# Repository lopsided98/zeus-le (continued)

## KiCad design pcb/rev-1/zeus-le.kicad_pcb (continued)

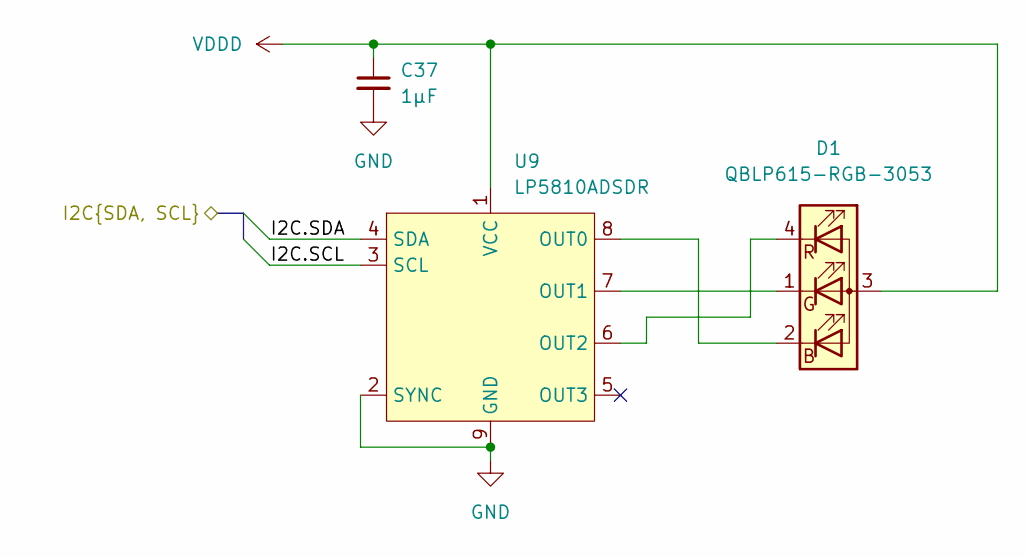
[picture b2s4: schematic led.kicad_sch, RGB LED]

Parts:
C37: 1µF; C_0603_1608Metric
D1: QBLP615-RGB-3053; LED_QBLP615-RGB-3053
U9: LP5810ADSDR; WSON-8-1EP_3x3mm_P0.65mm_EP1.65x2.4mm_ThermalVias

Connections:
/Audio/I2C.SCL: U9.3 (SCL); also elsewhere on the board
/Audio/I2C.SDA: U9.4 (SDA); also elsewhere on the board
GND: C37.2, U9.2 (SYNC), U9.9 (GND); also elsewhere on the board
unnamed: D1.2 (BK), U9.8 (OUT0)
unnamed: D1.1 (GK), U9.7 (OUT1)
unnamed: D1.4 (RK), U9.6 (OUT2)
VDDD: C37.1, D1.3 (A), U9.1 (VCC); also elsewhere on the board

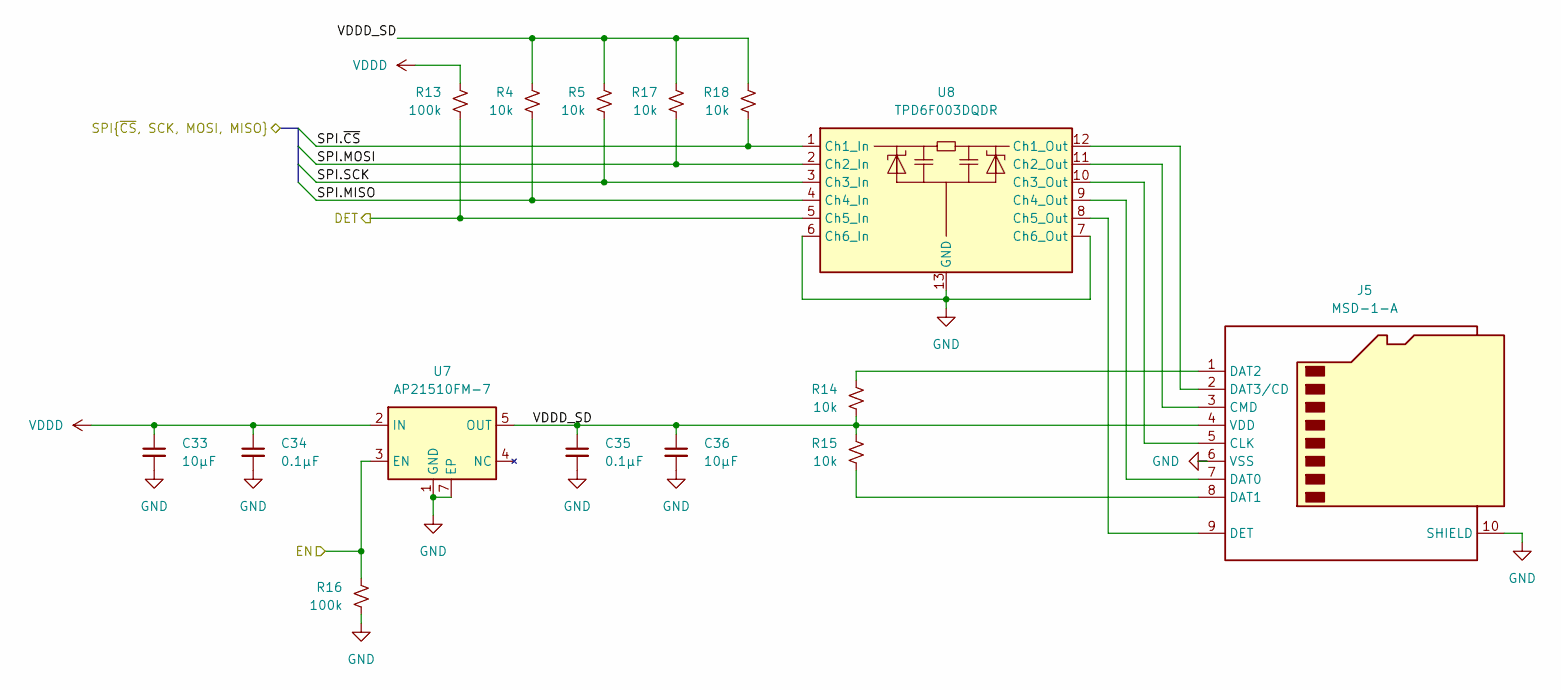
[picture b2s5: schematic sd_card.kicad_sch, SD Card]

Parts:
C33, C36: 10µF; C_0603_1608Metric
C34, C35: 0.1µF; C_0402_1005Metric
J5: MSD-1-A; microSD_HC_CUI_MSD-1-A
R4, R5, R14, R15, R17, R18: 10k; R_0402_1005Metric
R13, R16: 100k; R_0402_1005Metric
U7: AP21510FM-7; Diodes_UDFN2018-6
U8: TPD6F003DQDR; Texas_R-PWSON-N12_EP0.4x2mm; digikey# 296-25802-1-ND

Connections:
/MCU/SD.MISO: R4.2, U8.4 (Ch4_In); also elsewhere on the board
/MCU/SD.MOSI: R17.2, U8.2 (Ch2_In); also elsewhere on the board
/MCU/SD.SCK: R5.2, U8.3 (Ch3_In); also elsewhere on the board
/MCU/SD.~CS: R18.2, U8.1 (Ch1_In); also elsewhere on the board
/MCU/SD_DET: R13.2, U8.5 (Ch5_In); also elsewhere on the board
/MCU/SD_EN: R16.1, U7.3 (EN); also elsewhere on the board
/SD Card/VDDD_SD: C35.1, C36.1, J5.4 (VDD), R4.1, R5.1, R14.2, R15.1, R17.1, R18.1, U7.5 (OUT), U7.6 (OUT)
GND: C33.2, C34.2, C35.2, C36.2, J5.6 (VSS), J5.10 (SHIELD), R16.2, U7.1 (GND), U7.7 (EP), U8.6 (Ch6_In), U8.7 (Ch6_Out), U8.13 (GND); also elsewhere on the board
unnamed: J5.5 (CLK), U8.10 (Ch3_Out)
unnamed: J5.3 (CMD), U8.11 (Ch2_Out)
unnamed: J5.7 (DAT0), U8.9 (Ch4_Out)
unnamed: J5.8 (DAT1), R15.2
unnamed: J5.1 (DAT2), R14.1
unnamed: J5.2 (DAT3/CD), U8.12 (Ch1_Out)
unnamed: J5.9 (DET), U8.8 (Ch5_Out)
VDDD: C33.1, C34.1, R13.1, U7.2 (IN); also elsewhere on the board

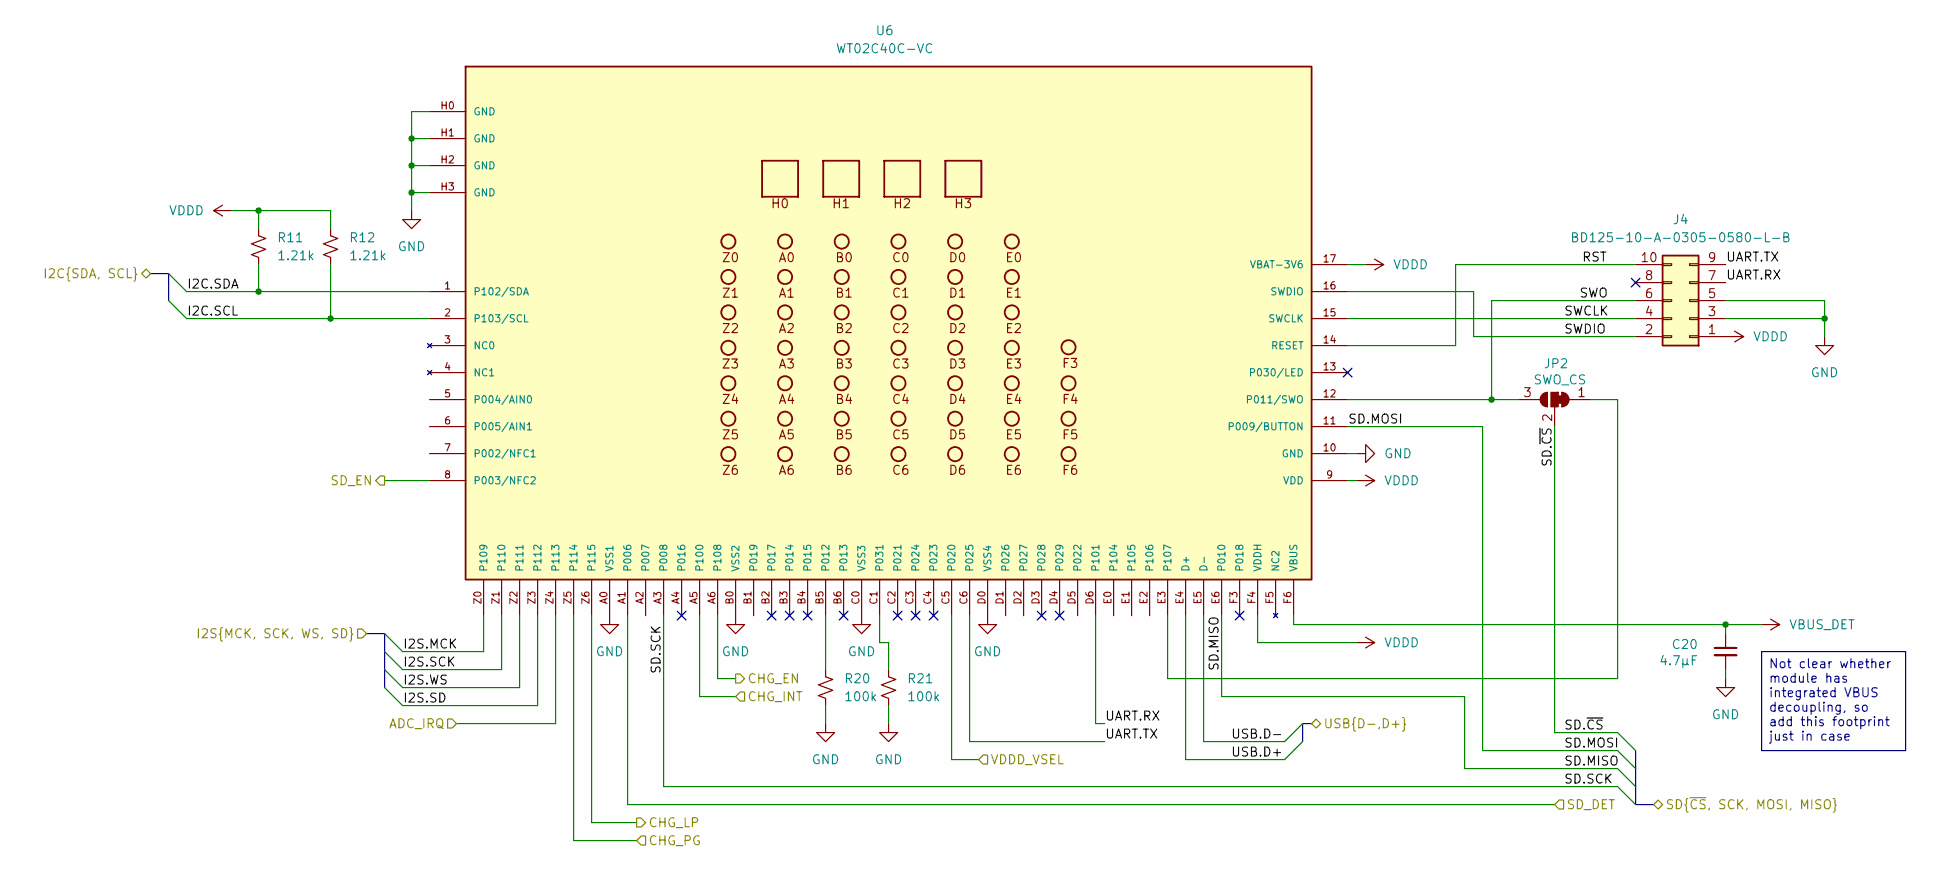
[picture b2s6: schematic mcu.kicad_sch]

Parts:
C20: 4.7µF; C_0603_1608Metric
J4: BD125-10-A-0305-0580-L-B; PinHeader_2x05_P1.27mm_Vertical_SMD
JP2: SWO_CS; SolderJumper-3_P2.0mm_Open_TrianglePad1.0x1.5mm
R11, R12: 1.21k; R_0402_1005Metric
R20, R21: 100k; R_0402_1005Metric
U6: WT02C40C-VC

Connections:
/Audio/I2C.SCL: R12.2, U6.2 (P103/SCL); also elsewhere on the board
/Audio/I2C.SDA: R11.2, U6.1 (P102/SDA); also elsewhere on the board
/Audio/I2S.MCK: U6.Z0 (P109); also elsewhere on the board
/Audio/I2S.SCK: U6.Z1 (P110); also elsewhere on the board
/Audio/I2S.SD: U6.Z3 (P112); also elsewhere on the board
/Audio/I2S.WS: U6.Z2 (P111); also elsewhere on the board
/Audio/IRQ: U6.Z4 (P113); also elsewhere on the board
/MCU/CHG_EN: U6.A6 (P108); also elsewhere on the board
/MCU/CHG_INT: U6.A5 (P100); also elsewhere on the board
/MCU/CHG_LP: U6.Z6 (P115); also elsewhere on the board
/MCU/CHG_PG: U6.Z5 (P114); also elsewhere on the board
/MCU/RST: J4.10, U6.14 (RESET)
/MCU/SD.MISO: U6.E6 (P010); also elsewhere on the board
/MCU/SD.MOSI: U6.11 (P009/BUTTON); also elsewhere on the board
/MCU/SD.SCK: U6.A3 (P008); also elsewhere on the board
/MCU/SD.~CS: JP2.2 (C); also elsewhere on the board
/MCU/SD_DET: U6.A1 (P006); also elsewhere on the board
/MCU/SD_EN: U6.8 (P003/NFC2); also elsewhere on the board
/MCU/SWCLK: J4.4, U6.15 (SWCLK)
/MCU/SWDIO: J4.2, U6.16 (SWDIO)
/MCU/SWO: J4.6, JP2.3 (B), U6.12 (P011/SWO)
/MCU/UART.RX: J4.7, U6.D6 (P101)
/MCU/UART.TX: J4.9, U6.C6 (P025)
/MCU/USB.D+: U6.E4 (D+); also elsewhere on the board
/MCU/USB.D-: U6.E5 (D-); also elsewhere on the board
/MCU/VDDD_VSEL: U6.C5 (P020); also elsewhere on the board
GND: C20.2, J4.3, J4.5, R20.2, R21.2, U6.10 (GND), U6.A0 (VSS1), U6.B0 (VSS2), U6.C0 (VSS3), U6.D0 (VSS4), U6.H0 (GND), U6.H1 (GND), U6.H2 (GND), U6.H3 (GND); also elsewhere on the board
unnamed: JP2.1 (A), U6.E3 (P107)
unnamed: R20.1, U6.B5 (P012)
unnamed: R21.1, U6.C1 (P031)
VBUS_DET: C20.1, U6.F6 (VBUS); also elsewhere on the board
VDDD: J4.1, R11.1, R12.1, U6.9 (VDD), U6.17 (VBAT-3V6), U6.F4 (VDDH); also elsewhere on the board

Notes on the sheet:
Not clear whether module has integrated VBUS decoupling, so add this footprint just in case

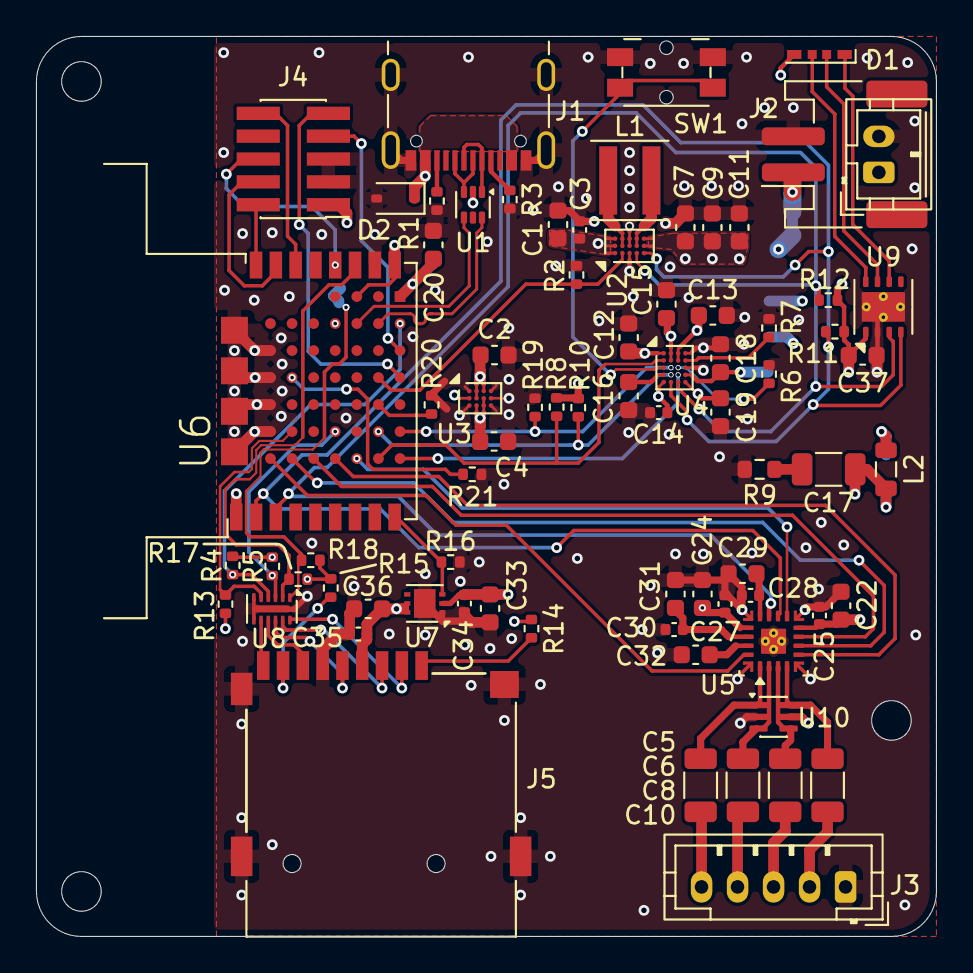
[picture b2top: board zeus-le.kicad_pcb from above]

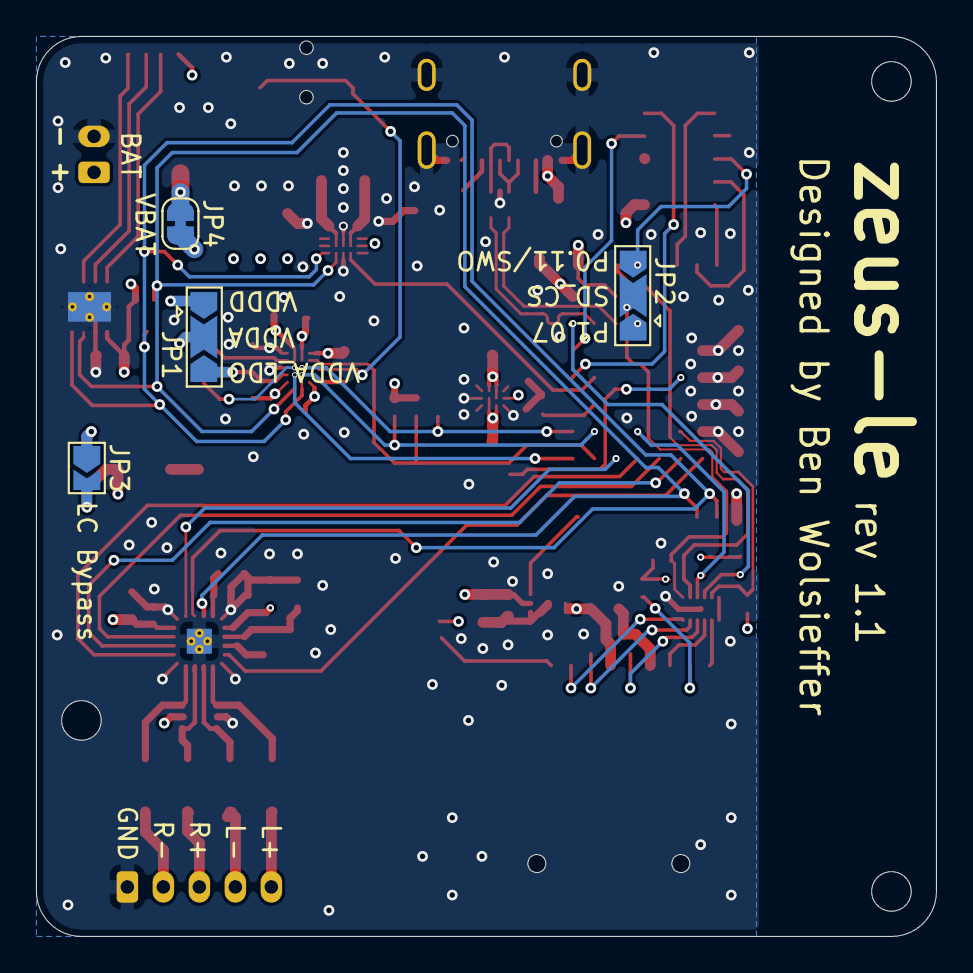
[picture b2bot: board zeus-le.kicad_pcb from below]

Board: 6 copper layers, 50.0 x 50.0 mm, 83 parts (4 on the bottom side), 73 nets.

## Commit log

2023-12-02 Empty firmware that builds.
2023-12-02 Add GitHub actions workflow.
2023-12-02 Add GPLv3 license.
2023-12-02 Move GitHub workflow to correct directory.
2023-12-02 Regenerate west.nix
2023-12-03 Fix Nix build
2023-12-03 Fix Nix hashes.
2023-12-12 Initial network core build.
2023-12-13 Fix Nix build.
2023-12-13 Basic advertising example that builds.
2023-12-29 WIP packet timing prototype.
2023-12-30 Rename openocd directory to tools
2023-12-30 Split out board specific config.
2023-12-30 central: net: hci_ipc: change info to debug logging
2023-12-30 Update to Zephyr master
2023-12-30 Use zephyr fork.
2023-12-30 Add BabbleSim support.
    It doesn't quite work because the simulated EGU is only a stub, but it
    builds.
2024-01-01 Fix timestamping of packets.
2024-01-02 Update west-nix to fix build.
2024-01-02 Update west-nix
2024-01-02 Rearrange common libraries
2024-01-24 Add audio board with timer frequency estimation.
2024-02-04 Add basic HFCLKAUDIO feedback control.
    Only frequency is controlled for now.
2024-02-04 freq_est_sim: fix matrix simulator
2024-02-04 Basic working phase controller.
2024-02-11 Add SGTL5000 driver
    Not yet fully tested. Only basic I2C functionality has been tested, not
    actual audio.
2024-02-14 Incomplete USB audio support
    I decided this was too much work for a debugging feature, so it will be
    removed.
2024-02-23 Send audio over network and add SD card
    Send raw audio data over UDP through the USB network interface.
    Additionally, add support for the SPI SD card.
2024-02-26 Fix simulator build.
2024-03-04 Add basic I2S simulation using ALSA
    Can't handle errors or triggers, but works for basic recording.
2024-03-04 Add lftpd
    This is the unmodified upstream source from:
    https://github.com/vonnieda/lftpd
    It is abandoned so I am just vendoring it for simplicity.
2024-03-17 Update Zephyr.
    Convert to HWMv2.
2024-03-17 Basically working FTP server
    Lots of other changes in here as well.
2024-03-17 Rename lftpd_io -> lftpd_path
2024-03-17 lftpd: get rid of _t typedefs
2024-03-18 lftpd: fix tests
2024-03-29 lftpd: catch out of space error
2024-03-30 simulator.sh: use tmux to run multiple instances
    Run both the central and app firmware in separate tmux panes.
2024-03-30 audio: add wav file support
    Not tested yet.
2024-03-30 Get central simulation working.
2024-04-13 Update Zephyr
2024-04-28 Basic recording working in simulator.
2024-04-28 Try to sync ADC sampling times
    Don't just keep sampling from drifting over time, try to eliminate any
    initial ADC sampling phase offset between different devices.
2024-04-28 audio: fix WAV bytes per frame
2024-04-28 Split files at 2 GiB
    Also, get rid of sscanf(), which isn't available in the minimal libc.
2024-04-28 Fix nRF53 build.
2024-04-28 Update west Nix sources.
2024-05-10 sgtl5000: fix chip configuration
2024-05-10 Working recording to SD card
2024-05-11 Only update WAV size every 10 seconds
2024-06-21 Initial version of the PCB
    This is pretty much done, except for designing the analog supply filter
    and replacing the USB PD/BC1.2 negotiation chip that cannot actually be
    purchased.
2024-06-21 pcb: fix LED 3D model file name
2024-06-30 pcb: simplify power supply and define LC filter
2024-07-06 pcb: pretty much the final version
2024-07-07 pcb: use debug connector with shroud
    This also gets the connector up higher so the cable won't hit the USB
    connector as much.
2024-07-07 pcb: rotate debug connector
    This prevents it from interfering with the USB connector.
2024-07-07 pcb: update fills
2024-07-20 pcb: rev 1.0 version submitted for manufacturing
2024-07-20 pcb: fix debug connector part number
2024-08-01 pcb: remove stray trace
2024-08-19 pcb: replace inductor
    Replace power supply inductor with a more readily available and cheaper
    part.
2024-08-23 Add board definition for custom PCB
2024-08-23 Temporarily disable audio to allow bringing up board without I2C
2024-08-23 Update zephyr.
    This version should support the nRF7002.
2024-08-23 actions: print full build log
    'nix build' has the stupid default of only showing the last few (usually
    irrelevant) lines.
2024-08-23 Add WiFi support
    WiFi is still slow (~1 Mbps) and uses almost all the RAM, but it works.
2024-08-24 Fix mbedtls hash and remove debugging code
2024-08-24 actions: update dependencies
2024-08-24 Fix central build on custom PCB
2024-08-24 Fix nRF53 Nix builds.
2024-08-24 Try to fix simulator Nix build
    It is almost working, but BabbleSim is not being built properly. It
    works fine in the shell through west.
2024-09-06 Add drivers for battery charger, LED and ADC
    Some of this is still WIP. Also, add an experimental caching layer to
    try to improve filesystem performance (doesn't help much, at least not
    with seeking).
2024-09-06 Add RT6160 driver.
2024-09-07 bq2515x: mask unused interrupts, disable watchdog
    The BQ2515X has a 50 second watchdog that resets all the charger
    parameters. This was causing the input current limit to be reset, which
    in turn caused the nRF7002 to brown out and stop working.
2024-09-07 lp58xx: make reset more reliable, prevent spurious LSD faults
    The datasheet recommends setting the LSD threshold to 0.65 VCC.
2024-09-07 bq2515x: add support for CE pin
2024-09-07 bq2515x: check CE pin value to determine status
2024-09-07 Don't use gpio_pin_get() to read output value
    It only works on inputs.
2024-09-09 record: fix mutex unlock when not initialized
2024-09-09 Only write WAV length at end.
    This avoids seeking which becomes progressively slower as the file gets
    larger. Also, adjust the buffering and thread priorities to try to
    reduce overruns.
2024-09-09 audio: split const and non-const data
    This allows the const data to be placed in flash and saves some RAM.
2024-09-14 Set CPU to 128 MHz, add some more logging
2024-09-17 bq2515x: support LP pin
    LP must be high to communicate over I2C when VIN is not connected.
2024-09-21 audio: move frequency update to audio thread
    The sync work item was sometimes getting delayed and causing the block
    time queue to be empty. There's no real reason to use a workqueue for
    this; it can be done in the audio thread.
2024-09-21 Fix audio sync sign errors
    central = local - theta
2024-09-21 audio: increase buffering
2024-09-22 disk_cache: fix memory corruption during flush
    There was a extra level of pointer passed to k_mem_slab_free()
2024-09-22 disk_cache: don't hardcode slab alignment
2024-09-22 Update zephyr fork.
2024-09-22 sd_card: support hotplugging
2024-09-25 Refactor wav library
    Improve file splitting and make sure we don't set the length to a
    partial sample if we run out of space.
2024-09-28 audio: add sync loss recovery
    If the central goes out of range temporarily or reboots, enable the
    audio node to reacquire the sync signal. Check if each measurement is an
    outlier and reset the state estimator if several outliers are received
    in a row. This should maintain sync continuity if the central only went
    out of range, but also adjust to the new central time reference if it
    rebooted.
2024-10-01 audio: add LED patterns for different states
2024-10-04 audio: add power on/off support
    Add support for turning power on/off by long pressing the button. While
    the device is off, the LED shows the charging status.
2024-10-05 audio: fix charge LED when VIN is connected while powered on
    Update the charge LED state when a charging event is detected.
2024-10-05 lp58xx: plural to singular units
2024-10-05 Add bq2515x_adc driver
    This allows reading the battery voltage, input voltage and input
    current.
2024-10-05 audio: add shell command for printing battery status
2024-10-05 Make led and power code common between audio and central
    Still needs some work to support unique LED patterns for central.
2024-10-05 wifi: use logical control for power pins
2024-10-06 Use a different LED color for central node
2024-10-06 Add forgotten common Kconfig
2024-10-06 Use a single IPC instance for all endpoints
    OpenAMP supports multiple endpoints so we might as well use this
    feature. This saves a little RAM and flash.
2024-10-06 Add support for starting/stopping on button press.
2024-10-07 Change audio format to 24-bit 48kHz
    I2S peripheral won't pack 24-bit words tightly, so we just use 32-bit
    and discard the low byte.
2024-10-11 Move battery shell command to common
    This requires a stupid hack to make the linker behave
    Also, flush the log before shutting down.
2024-10-11 power: enable VIN power good event
    This is used to update the charging state and was previously missing.
2024-10-20 Add save/restore of ADC gains
2024-10-20 Enable ADC power management.
    Put the ADC in sleep mode when not in use.
2024-10-20 central: increase button debounce delay
2024-10-20 central: fix LED record status on startup
2024-10-20 Synchronize LED pulses while recording
    Keep the periodic LED pulses while recording in sync on all devices.
2024-10-21 central: avoid triggering recording on startup
    Don't trigger a recording until the button has been released after
    startup.
2024-10-21 central: integrte with common shell commands
    Define central shell commands so the "zeus battery" command from the
    common library works as well.
2024-11-02 Change record LED color to red
2024-11-02 Increase charge current to 300mA
2024-11-03 audio: add input impedance setting
2024-11-03 audio: allow custom file prefix
    Also, allow booting with no SD card inserted.
2024-11-03 Update Zephyr to include SD card fix
2024-11-06 audio: increase audio thread stack size
    There was a stack overflow when splitting files.
2024-11-06 audio: add comment about splitting edge case
2024-11-10 Fix simulator build
    Use GPIO and I2C emulators get drivers to build. The emulators aren't
    implemented yet but this is enough to get the firmware to boot.
2024-11-10 dummy_codec: add get_property API
2024-11-23 Print file prefix as part of "zeus status"
2024-11-23 central: allow 16 paired devices
2024-12-10 pcb: add pull-downs for WiFi power
2024-12-11 pcb: apply changes from manufacturing
    * Increase WLCSP stencil clearance to -10%
    * Use SMD WLCSP pads, dimensions from JLCPCB gerbers
    * Copper margin around NPTH, only those in my library so far
2024-12-12 pcb: move rev-1 design to subdirectory
    The rev-2 design is not going to totally supersede the rev-1 design
    because they are different form factors. Therefore, keep rev-1 around
    in a separate directory.
2025-01-02 pcb: first draft of rev-2 PCB
2025-01-26 pcb: full rev-2 layout
    Mostly finished layout for the rev-2 board
2025-01-28 pcb: minor schematic cleanup
2025-02-15 pcb: update
    Mostly downsize several decoupling capacitors to save space
2025-03-10 Increase PSRAM size to 64Mbit
2025-03-13 audio: disable network stack to increase the buffer size a bit
    Disable network stack which is currently not used anyway in order to
    save a bit of memory and allow slightly bigger buffers.
2025-03-13 audio: record 16-bit samples
    This reduces the data rate and increases the available buffer time,
    which will hopefully help with buffer overruns.
2025-06-14 pcb: upgrade to KiCad 9.0
2025-11-02 pcb: rev-2: add missing 3D models, rev-1: update to KiCAD 9
2026-05-24 Mark LTspice models as data for linguist (GitHub)
    This should fix the language statistics on GitHub.
2026-05-24 Add README
2026-05-25 Update PCBs
    * Update to KiCad 10
    * Update footprint for nRF53 module based on 1.01 datasheet with
    actually readable mechanical drawing
    * Add 3D model for production nRF53 module
    * Remove overlapping silkscreen on rev-1 with production nRF53 module
2026-05-25 Add PCB render to README
2026-06-08 actions: upgrade dependencies using ratchet
